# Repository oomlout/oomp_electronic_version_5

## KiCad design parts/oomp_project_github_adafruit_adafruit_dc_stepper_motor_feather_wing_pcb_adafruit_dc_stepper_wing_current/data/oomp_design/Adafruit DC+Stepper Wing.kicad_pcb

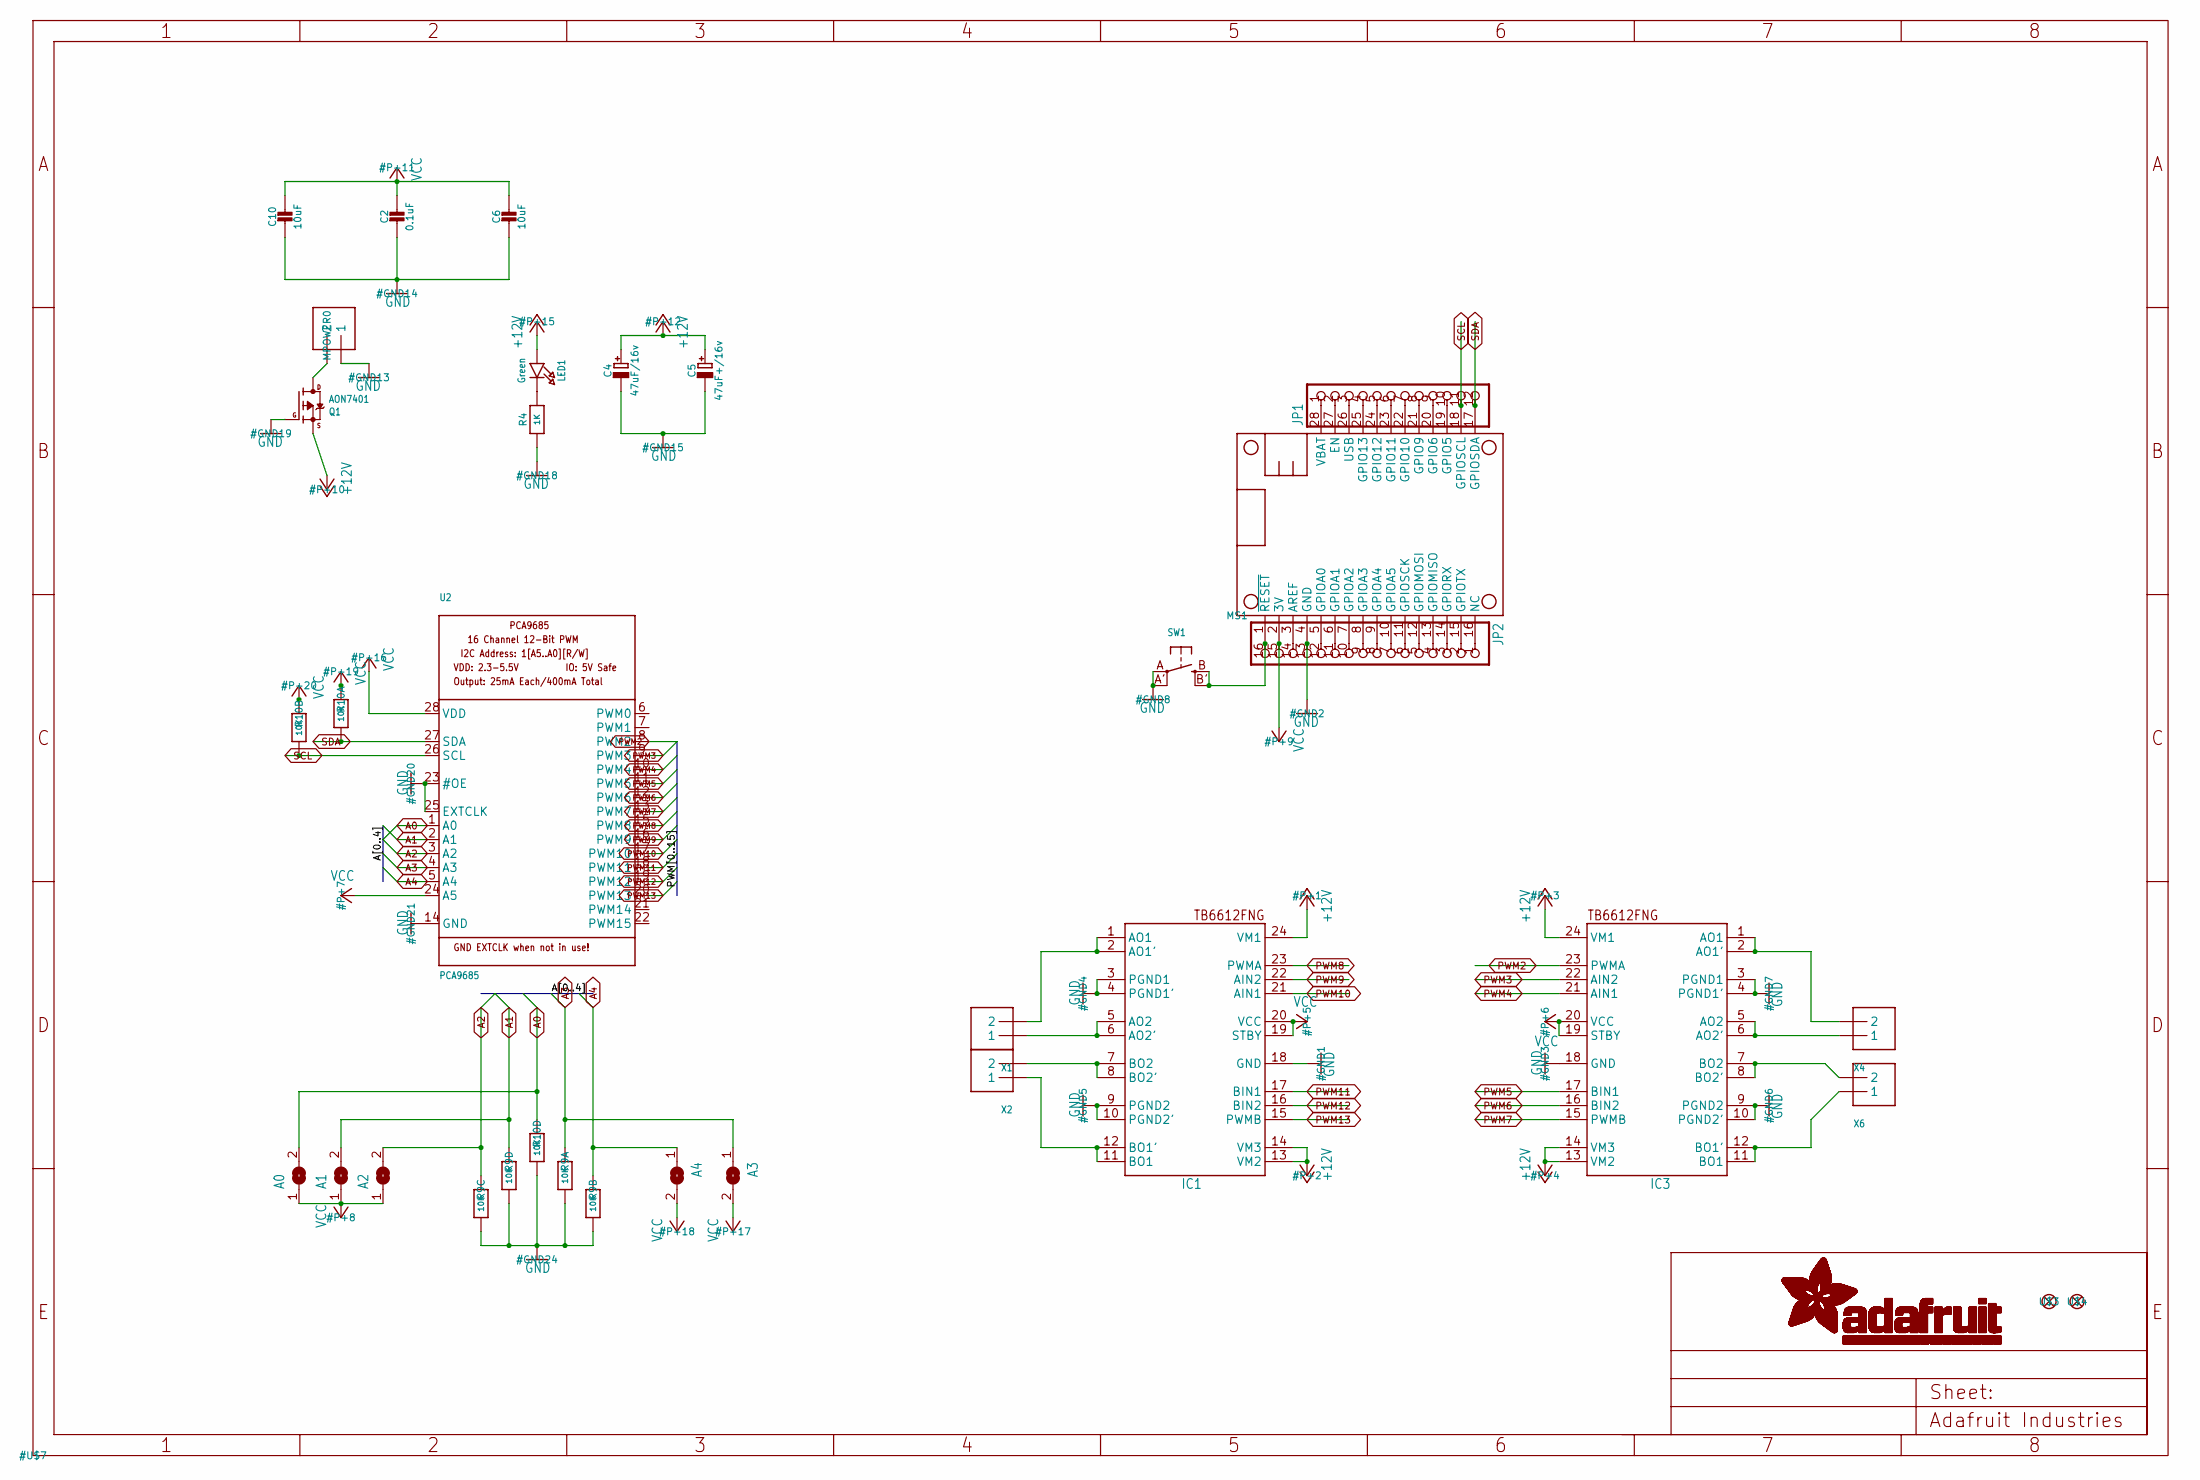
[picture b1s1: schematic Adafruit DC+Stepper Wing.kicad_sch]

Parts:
A0, A1, A2, A3, A4: SOLDERJUMPERREFLOW_NOPASTE; SOLDERJUMPER_REFLOW_NOPASTE
C2: 0.1uF; 0805-NO
C4: 47uF/16v; PANASONIC_C
C5: 47uF+/16v; PANASONIC_C
C6, C10: 10uF; 0805-NO
IC1, IC3: TB6612FNG; SSOP24
JP1: HEADER-1X12; 1X12_ROUND
JP2: HEADER-1X16ROUND; 1X16_ROUND
LED1: Green; CHIPLED_0805_NOOUTLINE
MPOWER0: 1X2-3.5MM
MS1: FEATHERWING
Q1: AON7401; POWERDI3333
R4: 1K; 0805-NO
R9, R10: 10K; RESPACK_4X0603
SW1: SWITCH_TACT_SMT4.6X2.8; BTN_KMR2_4.6X2.8
U2: PCA9685; TSSOP28
U$3, U$4: FIDUCIAL""; FIDUCIAL_1MM
X1, X2, X4, X6: TERMBLOCK_1X2; TERMBLOCK_1X2-3.5MM

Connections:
+12V: C4.+, C5.+, IC1.13 (VM2), IC1.14 (VM3), IC1.24 (VM1), IC3.13 (VM2), IC3.14 (VM3), IC3.24 (VM1), LED1.A, Q1.1 (S), Q1.2 (S), Q1.3 (S)
A0: A0.2, R10.4 (1), U2.1 (A0)
A1: A1.2, R9.5 (2), U2.2 (A1)
A2: A2.2, R9.6 (2), U2.3 (A2)
A3: A3.1, R9.8 (2), U2.4 (A3)
A4: A4.1, R9.7 (2), U2.5 (A4)
GND: C2.2, C4.-, C5.-, C6.2, C10.2, IC1.3 (PGND1), IC1.4 (PGND1'), IC1.9 (PGND2), IC1.10 (PGND2'), IC1.18 (GND), IC3.3 (PGND1), IC3.4 (PGND1'), IC3.9 (PGND2), IC3.10 (PGND2'), IC3.18 (GND), JP2.13, MPOWER0.1, MS1.4 (GND), Q1.4 (G), R4.1, R9.1, R9.2 (1), R9.3 (1), R9.4 (1), R10.5 (2), SW1.A, SW1.A' (P1), U2.14 (GND), U2.23 (#OE), U2.25 (EXTCLK)
unnamed: JP1.2, MS1.27 (EN)
unnamed: JP1.4, MS1.25 (GPIO13)
unnamed: MPOWER0.2, Q1.5678 (D)
unnamed: IC1.1 (AO1), IC1.2 (AO1'), X1.2
unnamed: JP1.5, MS1.24 (GPIO12)
unnamed: IC1.5 (AO2), IC1.6 (AO2'), X1.1
unnamed: IC1.7 (BO2), IC1.8 (BO2'), X2.2
unnamed: JP1.6, MS1.23 (GPIO11)
unnamed: IC1.11 (BO1), IC1.12 (BO1'), X2.1
unnamed: JP1.7, MS1.22 (GPIO10)
unnamed: JP1.8, MS1.21 (GPIO9)
unnamed: IC3.1 (AO1), IC3.2 (AO1'), X4.2
unnamed: JP1.9, MS1.20 (GPIO6)
unnamed: IC3.5 (AO2), IC3.6 (AO2'), X4.1
unnamed: IC3.7 (BO2), IC3.8 (BO2'), X6.2
unnamed: JP1.10, MS1.19 (GPIO5)
unnamed: IC3.11 (BO1), IC3.12 (BO1'), X6.1
unnamed: JP2.1, MS1.16 (NC)
unnamed: JP2.2, MS1.15 (GPIOTX)
unnamed: JP2.3, MS1.14 (GPIORX)
unnamed: JP2.4, MS1.13 (GPIOMISO)
unnamed: JP2.5, MS1.12 (GPIOMOSI)
unnamed: JP2.6, MS1.11 (GPIOSCK)
unnamed: JP2.7, MS1.10 (GPIOA5)
unnamed: JP2.8, MS1.9 (GPIOA4)
unnamed: JP2.9, MS1.8 (GPIOA3)
unnamed: JP2.10, MS1.7 (GPIOA2)
unnamed: JP2.11, MS1.6 (GPIOA1)
unnamed: JP2.12, MS1.5 (GPIOA0)
unnamed: JP2.14, MS1.3 (AREF)
unnamed: JP2.16, MS1.1 (~RESET), SW1.B (S), SW1.B' (S1)
unnamed: LED1.C, R4.2
PWM2: IC3.23 (PWMA), U2.8 (PWM2)
PWM3: IC3.22 (AIN2), U2.9 (PWM3)
PWM4: IC3.21 (AIN1), U2.10 (PWM4)
PWM5: IC3.17 (BIN1), U2.11 (PWM5)
PWM6: IC3.16 (BIN2), U2.12 (PWM6)
PWM7: IC3.15 (PWMB), U2.13 (PWM7)
PWM8: IC1.23 (PWMA), U2.15 (PWM8)
PWM9: IC1.22 (AIN2), U2.16 (PWM9)
PWM10: IC1.21 (AIN1), U2.17 (PWM10)
PWM11: IC1.17 (BIN1), U2.18 (PWM11)
PWM12: IC1.16 (BIN2), U2.19 (PWM12)
PWM13: IC1.15 (PWMB), U2.20 (PWM13)
SCL: JP1.11, MS1.18 (GPIOSCL), R10.2 (1), U2.26 (SCL)
SDA: JP1.12, MS1.17 (GPIOSDA), R10.1, U2.27 (SDA)
USB: JP1.3, MS1.26 (USB)
VBAT: JP1.1, MS1.28 (VBAT)
VCC: A0.1, A1.1, A2.1, A3.2, A4.2, C2.1, C6.1, C10.1, IC1.19 (STBY), IC1.20 (VCC), IC3.19 (STBY), IC3.20 (VCC), JP2.15, MS1.2 (3V), R10.7 (2), R10.8 (2), U2.24 (A5), U2.28 (VDD)

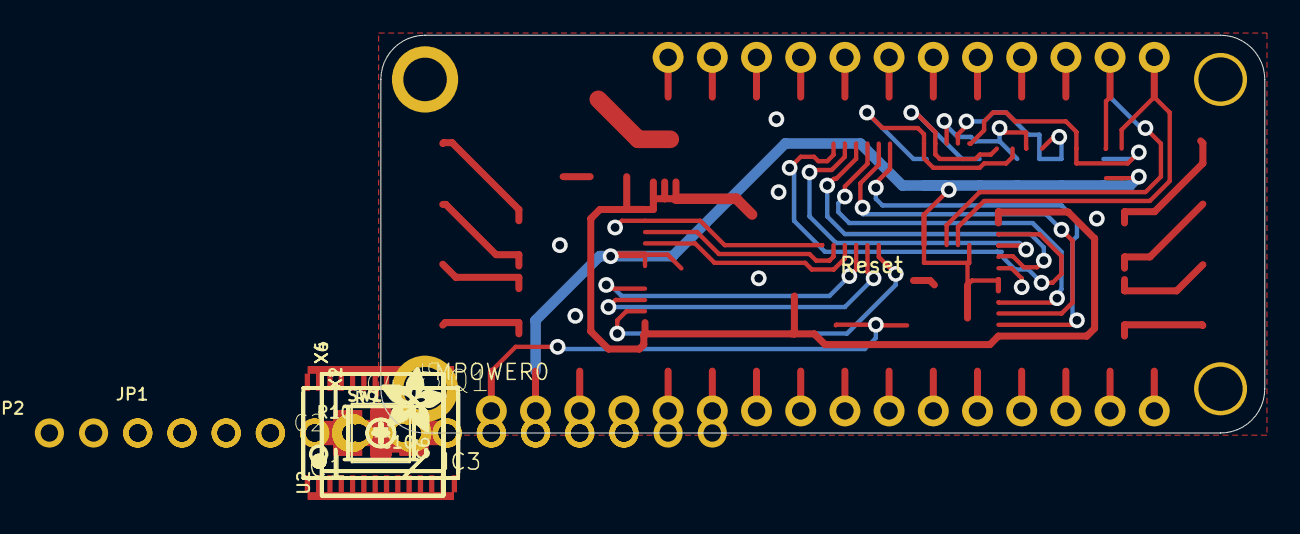
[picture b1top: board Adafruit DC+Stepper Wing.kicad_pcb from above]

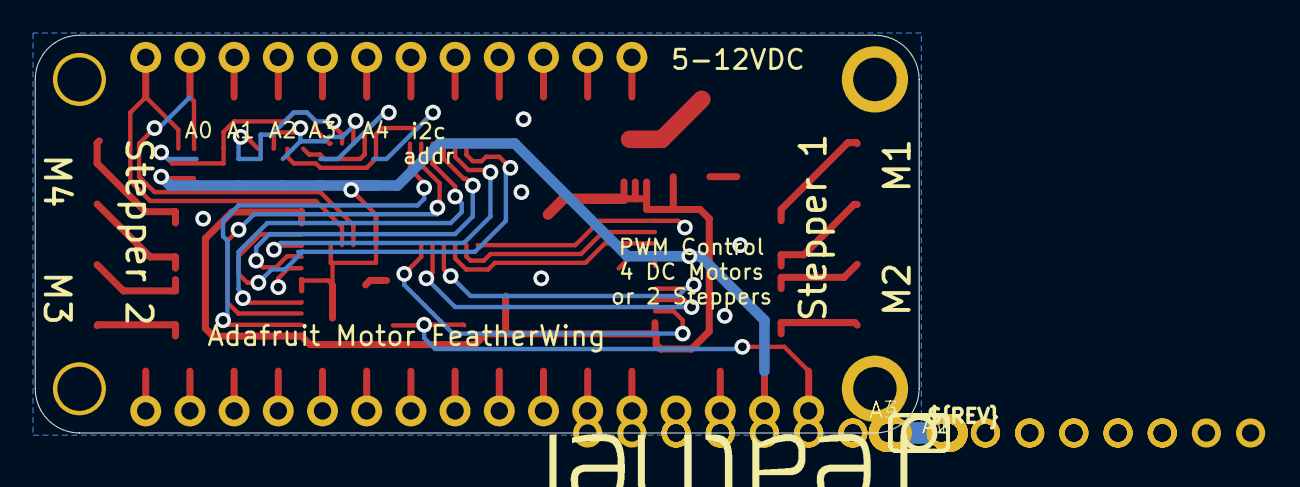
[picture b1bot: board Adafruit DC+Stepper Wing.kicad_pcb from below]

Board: 16 copper layers, 50.8 x 22.9 mm, 34 parts (7 on the bottom side), 56 nets.

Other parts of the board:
U$1: SYMBOL_PLUS
U$2: SYMBOL_MINUS
U$5: ADAFRUIT_3.5MM
U$6: FEATHERLOGO
U$8: PCBFEAT-REV-040

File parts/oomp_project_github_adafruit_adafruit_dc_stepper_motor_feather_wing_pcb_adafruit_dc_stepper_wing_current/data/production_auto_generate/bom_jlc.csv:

Comment,Designator,Footprint,LCSC Part #
,JP1,Adafruit DC+Stepper Wing-import-fps:1X12_ROUND,C7501588
,JP2,Adafruit DC+Stepper Wing-import-fps:1X16_ROUND,C7501270
,U$5,Adafruit DC+Stepper Wing-import-fps:ADAFRUIT_3.5MM,
,SW1,Adafruit DC+Stepper Wing-import-fps:BTN_KMR2_4.6X2.8,
,U$6,Adafruit DC+Stepper Wing-import-fps:FEATHERLOGO,
,U$8,Adafruit DC+Stepper Wing-import-fps:PCBFEAT-REV-040,
,"A0,A1,A2,A3,A4",Adafruit DC+Stepper Wing-import-fps:SOLDERJUMPER_REFLOW_NOPASTE,
,U$2,Adafruit DC+Stepper Wing-import-fps:SYMBOL_MINUS,
,U$1,Adafruit DC+Stepper Wing-import-fps:SYMBOL_PLUS,
,"X1,X2,X4,X6",Adafruit DC+Stepper Wing-import-fps:TERMBLOCK_1X2-3.5MM,
0.1uF,C2,Adafruit DC+Stepper Wing-import-fps:0805-NO,
10K,"R9,R10",Adafruit DC+Stepper Wing-import-fps:RESPACK_4X0603,C98220
10uF,"C6,C10",Adafruit DC+Stepper Wing-import-fps:0805-NO,
1K,R4,Adafruit DC+Stepper Wing-import-fps:0805-NO,C17513
1X2-3.5MM,MPOWER0,Adafruit DC+Stepper Wing-import-fps:1X2-3.5MM,C492401
47uF+/16v,C5,Adafruit DC+Stepper Wing-import-fps:PANASONIC_C,
47uF/16v,C4,Adafruit DC+Stepper Wing-import-fps:PANASONIC_C,
AON7401,Q1,Adafruit DC+Stepper Wing-import-fps:POWERDI3333,
FEATHERWING,MS1,Adafruit DC+Stepper Wing-import-fps:FEATHERWING,
"FIDUCIAL""""","U$3,U$4",Adafruit DC+Stepper Wing-import-fps:FIDUCIAL_1MM,
Green,LED1,Adafruit DC+Stepper Wing-import-fps:CHIPLED_0805_NOOUTLINE,
PCA9685,U2,Adafruit DC+Stepper Wing-import-fps:TSSOP28,
TB6612FNG,"IC1,IC3",Adafruit DC+Stepper Wing-import-fps:SSOP24,

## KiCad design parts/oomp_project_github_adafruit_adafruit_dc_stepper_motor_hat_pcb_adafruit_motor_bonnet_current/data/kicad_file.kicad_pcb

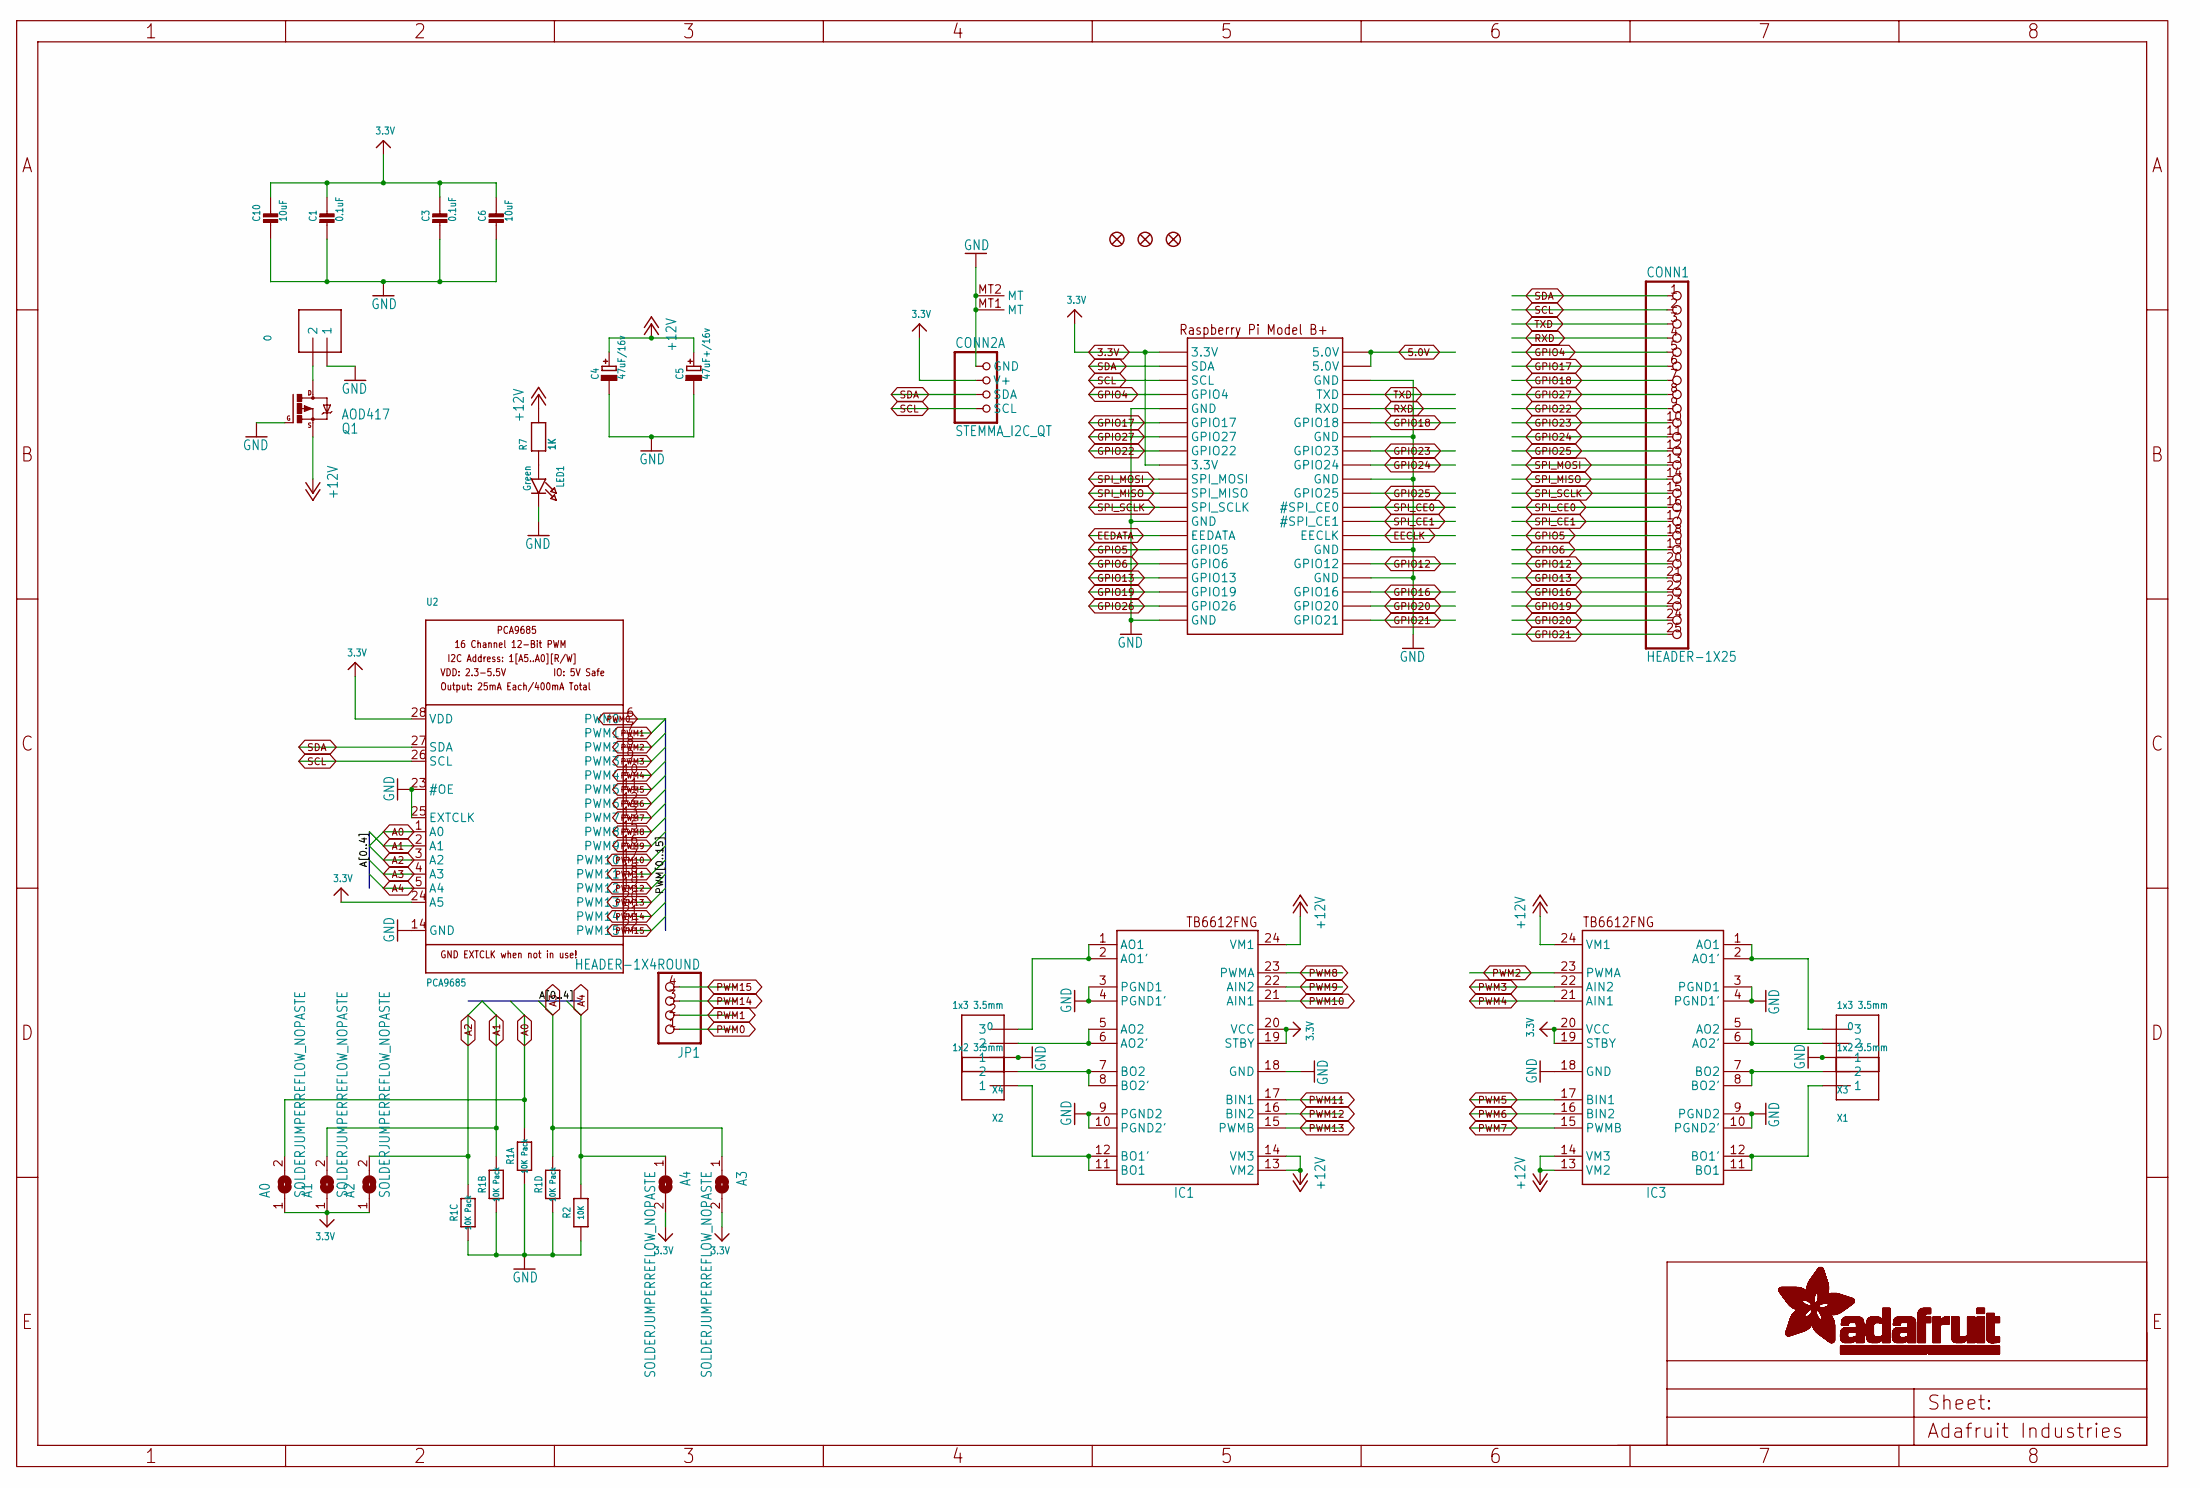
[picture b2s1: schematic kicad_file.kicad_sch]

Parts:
A0, A1, A2, A3, A4: SOLDERJUMPERREFLOW_NOPASTE; SOLDERJUMPER_REFLOW_NOPASTE
C1, C3: 0.1uF; 0603-NO
C4: 47uF/16v; PANASONIC_C
C5: 47uF+/16v; PANASONIC_C
C6, C10: 10uF; 0805-NO
CONN1: HEADER-1X25; 1X25_ROUND_70MIL
CONN2: STEMMA_I2C_QT; JST_SH4; LCSC C2905006
FID1, FID2, FID3: FIDUCIAL_1MM
IC1, IC3: TB6612FNG; SSOP24
JP1: HEADER-1X4ROUND; 1X04_ROUND
LED1: Green; CHIPLED_0805_NOOUTLINE
MPOWER0: 1x2 3.5mm; TERMBLOCK_1X2-3.5MM
Q1: AOD417; D-PAK_TO252AA
R1: 10K Pack; RESPACK_4X0603
R2: 10K; 0603-NO
R7: 1K; 0603-NO
RPI1: RASPBERRYPI_BPLUS_BONNET_THMSMT; PI_BONNET_THMSMT
U2: PCA9685; TSSOP28
X1, X2: 1x2 3.5mm; TERMBLOCK_1X2-3.5MM
X3, X4: 1x3 3.5mm; TERMBLOCK_1X3-3.5MM

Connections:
3.3V: A0.1, A1.1, A2.1, A3.2, A4.2, C1.1, C3.1, C6.1, C10.1, CONN2.2 (V+), IC1.19 (STBY), IC1.20 (VCC), IC3.19 (STBY), IC3.20 (VCC), RPI1.1 (3.3V), RPI1.17 (3.3V), RPI1.S1 (3.3V), RPI1.S17 (3.3V), U2.24 (A5), U2.28 (VDD)
5.0V: RPI1.2 (5.0V), RPI1.4 (5.0V), RPI1.S2 (5.0V), RPI1.S4 (5.0V)
+12V: C4.+, C5.+, IC1.13 (VM2), IC1.14 (VM3), IC1.24 (VM1), IC3.13 (VM2), IC3.14 (VM3), IC3.24 (VM1), Q1.3 (S), R7.2
A0: A0.2, R1.8 (2), U2.1 (A0)
A1: A1.2, R1.7 (2), U2.2 (A1)
A2: A2.2, R1.6 (2), U2.3 (A2)
A3: A3.1, R1.5 (2), U2.4 (A3)
A4: A4.1, R2.2, U2.5 (A4)
EECLK: RPI1.28 (EECLK), RPI1.S28 (EECLK)
EEDATA: RPI1.27 (EEDATA), RPI1.S27 (EEDATA)
GND: C1.2, C3.2, C4.-, C5.-, C6.2, C10.2, CONN2.1 (GND), CONN2.MT1 (MT), CONN2.MT2 (MT), IC1.3 (PGND1), IC1.4 (PGND1'), IC1.9 (PGND2), IC1.10 (PGND2'), IC1.18 (GND), IC3.3 (PGND1), IC3.4 (PGND1'), IC3.9 (PGND2), IC3.10 (PGND2'), IC3.18 (GND), LED1.C, MPOWER0.1, Q1.1 (G), R1.1, R1.2 (1), R1.3 (1), R1.4 (1), R2.1, RPI1.6 (GND), RPI1.9 (GND), RPI1.14 (GND), RPI1.20 (GND), RPI1.25 (GND), RPI1.30 (GND), RPI1.34 (GND), RPI1.39 (GND), RPI1.S6 (GND), RPI1.S9 (GND), RPI1.S14 (GND), RPI1.S20 (GND), RPI1.S25 (GND), RPI1.S30 (GND), RPI1.S34 (GND), RPI1.S39 (GND), U2.14 (GND), U2.23 (#OE), U2.25 (EXTCLK), X3.1, X4.1
GPIO4: CONN1.5, RPI1.7 (GPIO4), RPI1.S7 (GPIO4)
GPIO5: CONN1.18, RPI1.29 (GPIO5), RPI1.S29 (GPIO5)
GPIO6: CONN1.19, RPI1.31 (GPIO6), RPI1.S31 (GPIO6)
GPIO12: CONN1.20, RPI1.32 (GPIO12), RPI1.S32 (GPIO12)
GPIO13: CONN1.21, RPI1.33 (GPIO13), RPI1.S33 (GPIO13)
GPIO16: CONN1.22, RPI1.36 (GPIO16), RPI1.S36 (GPIO16)
GPIO17: CONN1.6, RPI1.11 (GPIO17), RPI1.S11 (GPIO17)
GPIO18: CONN1.7, RPI1.12 (GPIO18), RPI1.S12 (GPIO18)
GPIO19: CONN1.23, RPI1.35 (GPIO19), RPI1.S35 (GPIO19)
GPIO20: CONN1.24, RPI1.38 (GPIO20), RPI1.S38 (GPIO20)
GPIO21: CONN1.25, RPI1.40 (GPIO21), RPI1.S40 (GPIO21)
GPIO22: CONN1.9, RPI1.15 (GPIO22), RPI1.S15 (GPIO22)
GPIO23: CONN1.10, RPI1.16 (GPIO23), RPI1.S16 (GPIO23)
GPIO24: CONN1.11, RPI1.18 (GPIO24), RPI1.S18 (GPIO24)
GPIO25: CONN1.12, RPI1.22 (GPIO25), RPI1.S22 (GPIO25)
GPIO26: RPI1.37 (GPIO26), RPI1.S37 (GPIO26)
GPIO27: CONN1.8, RPI1.13 (GPIO27), RPI1.S13 (GPIO27)
M1A: IC1.1 (AO1), IC1.2 (AO1'), X4.3
M1B: IC1.5 (AO2), IC1.6 (AO2'), X4.2
M2A: IC1.11 (BO1), IC1.12 (BO1'), X2.1
M2B: IC1.7 (BO2), IC1.8 (BO2'), X2.2
M3A: IC3.1 (AO1), IC3.2 (AO1'), X3.3
M3B: IC3.5 (AO2), IC3.6 (AO2'), X3.2
M4A: IC3.11 (BO1), IC3.12 (BO1'), X1.1
M4B: IC3.7 (BO2), IC3.8 (BO2'), X1.2
unnamed: LED1.A, R7.1
PWM0: JP1.1, U2.6 (PWM0)
PWM1: JP1.2, U2.7 (PWM1)
PWM2: IC3.23 (PWMA), U2.8 (PWM2)
PWM3: IC3.22 (AIN2), U2.9 (PWM3)
PWM4: IC3.21 (AIN1), U2.10 (PWM4)
PWM5: IC3.17 (BIN1), U2.11 (PWM5)
PWM6: IC3.16 (BIN2), U2.12 (PWM6)
PWM7: IC3.15 (PWMB), U2.13 (PWM7)
PWM8: IC1.23 (PWMA), U2.15 (PWM8)
PWM9: IC1.22 (AIN2), U2.16 (PWM9)
PWM10: IC1.21 (AIN1), U2.17 (PWM10)
PWM11: IC1.17 (BIN1), U2.18 (PWM11)
PWM12: IC1.16 (BIN2), U2.19 (PWM12)
PWM13: IC1.15 (PWMB), U2.20 (PWM13)
PWM14: JP1.3, U2.21 (PWM14)
PWM15: JP1.4, U2.22 (PWM15)
RXD: CONN1.4, RPI1.10 (RXD), RPI1.S10 (RXD)
SCL: CONN1.2, CONN2.4 (SCL), RPI1.5 (SCL), RPI1.S5 (SCL), U2.26 (SCL)
SDA: CONN1.1, CONN2.3 (SDA), RPI1.3 (SDA), RPI1.S3 (SDA), U2.27 (SDA)
SPI_CE0: CONN1.16, RPI1.24 (#SPI_CE0), RPI1.S24 (#SPI_CE0)
SPI_CE1: CONN1.17, RPI1.26 (#SPI_CE1), RPI1.S26 (#SPI_CE1)
SPI_MISO: CONN1.14, RPI1.21 (SPI_MISO), RPI1.S21 (SPI_MISO)
SPI_MOSI: CONN1.13, RPI1.19 (SPI_MOSI), RPI1.S19 (SPI_MOSI)
SPI_SCLK: CONN1.15, RPI1.23 (SPI_SCLK), RPI1.S23 (SPI_SCLK)
TXD: CONN1.3, RPI1.8 (TXD), RPI1.S8 (TXD)
VMOTOR: MPOWER0.2, Q1.4 (D)

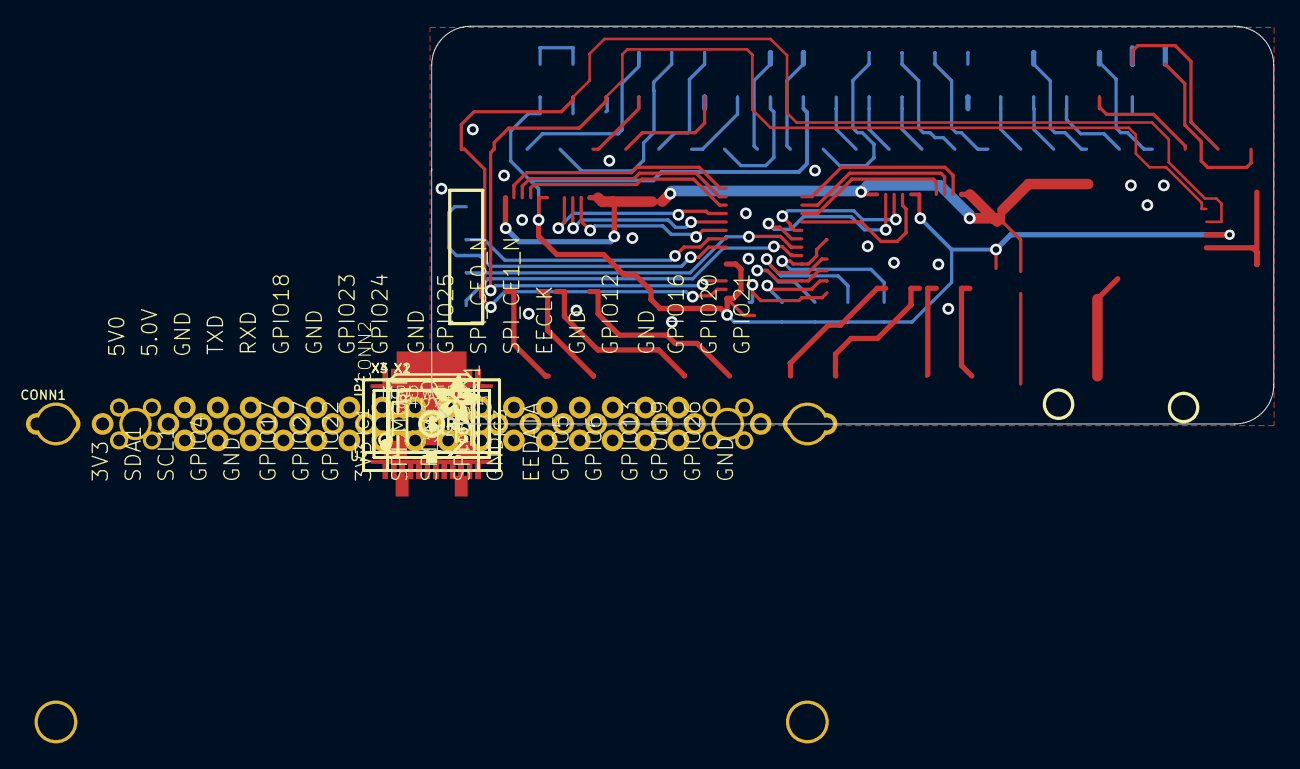
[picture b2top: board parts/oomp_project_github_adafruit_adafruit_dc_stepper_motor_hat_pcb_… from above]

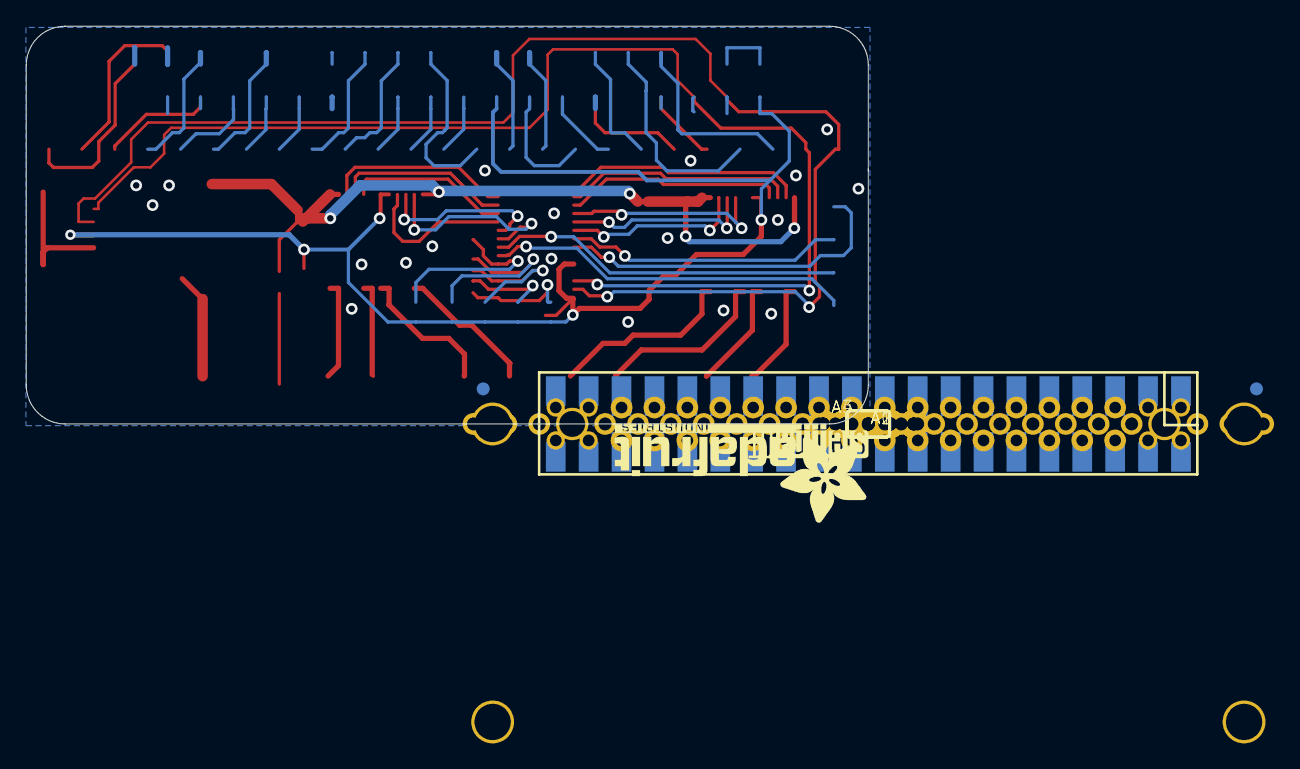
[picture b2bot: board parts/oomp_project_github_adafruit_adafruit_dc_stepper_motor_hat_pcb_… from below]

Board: 2 copper layers, 65.0 x 30.7 mm, 82 parts (13 on the bottom side), 63 nets.

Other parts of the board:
PLABEL0: PLABEL0
PLABEL1: PLABEL1
PLABEL2: PLABEL2
PLABEL3: PLABEL3
PLABEL4: PLABEL4
PLABEL5: PLABEL5
PLABEL6: PLABEL6
PLABEL7: PLABEL7
PLABEL8: PLABEL8
PLABEL9: PLABEL9
PLABEL10: PLABEL10
PLABEL11: PLABEL11
PLABEL12: PLABEL12
PLABEL13: PLABEL13
PLABEL14: PLABEL14
PLABEL15: PLABEL15
PLABEL16: PLABEL16
PLABEL17: PLABEL17
PLABEL18: PLABEL18
PLABEL19: PLABEL19
PLABEL20: PLABEL20
PLABEL21: PLABEL21
PLABEL22: PLABEL22
PLABEL23: PLABEL23
PLABEL24: PLABEL24
PLABEL25: PLABEL25
PLABEL26: PLABEL26
PLABEL27: PLABEL27
PLABEL28: PLABEL28
PLABEL29: PLABEL29
PLABEL30: PLABEL30
PLABEL31: PLABEL31
PLABEL33: PLABEL33
PLABEL34: PLABEL34
PLABEL35: PLABEL35
PLABEL36: PLABEL36
PLABEL37: PLABEL37
PLABEL38: PLABEL38
PLABEL39: PLABEL39
PLABEL40: PLABEL40
PLABEL41: PLABEL41
PLABEL42: PLABEL42
PLABEL43: PLABEL43
PLABEL44: PLABEL44
PLABEL45: PLABEL45
PLABEL46: PLABEL46
PLABEL47: PLABEL47
U$6: PCBFEAT-REV-040
U$8: ADAFRUIT_TEXT_20MM
U$14: ADAFRUIT_3.5MM
U$15: STEMMAQT

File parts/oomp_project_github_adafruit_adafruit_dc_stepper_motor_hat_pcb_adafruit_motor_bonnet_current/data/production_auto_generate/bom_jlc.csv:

Comment,Designator,Footprint,LCSC Part #
,JP1,Adafruit Motor Bonnet Rev B-import-fps:1X04_ROUND,C42431795
,U$14,Adafruit Motor Bonnet Rev B-import-fps:ADAFRUIT_3.5MM,
,U$8,Adafruit Motor Bonnet Rev B-import-fps:ADAFRUIT_TEXT_20MM,
,U$6,Adafruit Motor Bonnet Rev B-import-fps:PCBFEAT-REV-040,
,PLABEL0,Adafruit Motor Bonnet Rev B-import-fps:PLABEL0,
,PLABEL1,Adafruit Motor Bonnet Rev B-import-fps:PLABEL1,
,PLABEL10,Adafruit Motor Bonnet Rev B-import-fps:PLABEL10,
,PLABEL11,Adafruit Motor Bonnet Rev B-import-fps:PLABEL11,
,PLABEL12,Adafruit Motor Bonnet Rev B-import-fps:PLABEL12,
,PLABEL13,Adafruit Motor Bonnet Rev B-import-fps:PLABEL13,
,PLABEL14,Adafruit Motor Bonnet Rev B-import-fps:PLABEL14,
,PLABEL15,Adafruit Motor Bonnet Rev B-import-fps:PLABEL15,
,PLABEL16,Adafruit Motor Bonnet Rev B-import-fps:PLABEL16,
,PLABEL17,Adafruit Motor Bonnet Rev B-import-fps:PLABEL17,
,PLABEL18,Adafruit Motor Bonnet Rev B-import-fps:PLABEL18,
,PLABEL19,Adafruit Motor Bonnet Rev B-import-fps:PLABEL19,
,PLABEL2,Adafruit Motor Bonnet Rev B-import-fps:PLABEL2,
,PLABEL20,Adafruit Motor Bonnet Rev B-import-fps:PLABEL20,
,PLABEL21,Adafruit Motor Bonnet Rev B-import-fps:PLABEL21,
,PLABEL22,Adafruit Motor Bonnet Rev B-import-fps:PLABEL22,
,PLABEL23,Adafruit Motor Bonnet Rev B-import-fps:PLABEL23,
,PLABEL24,Adafruit Motor Bonnet Rev B-import-fps:PLABEL24,
,PLABEL25,Adafruit Motor Bonnet Rev B-import-fps:PLABEL25,
,PLABEL26,Adafruit Motor Bonnet Rev B-import-fps:PLABEL26,
,PLABEL27,Adafruit Motor Bonnet Rev B-import-fps:PLABEL27,
,PLABEL28,Adafruit Motor Bonnet Rev B-import-fps:PLABEL28,
,PLABEL29,Adafruit Motor Bonnet Rev B-import-fps:PLABEL29,
,PLABEL3,Adafruit Motor Bonnet Rev B-import-fps:PLABEL3,
,PLABEL30,Adafruit Motor Bonnet Rev B-import-fps:PLABEL30,
,PLABEL31,Adafruit Motor Bonnet Rev B-import-fps:PLABEL31,
,PLABEL33,Adafruit Motor Bonnet Rev B-import-fps:PLABEL33,
,PLABEL34,Adafruit Motor Bonnet Rev B-import-fps:PLABEL34,
,PLABEL35,Adafruit Motor Bonnet Rev B-import-fps:PLABEL35,
,PLABEL36,Adafruit Motor Bonnet Rev B-import-fps:PLABEL36,
,PLABEL37,Adafruit Motor Bonnet Rev B-import-fps:PLABEL37,
,PLABEL38,Adafruit Motor Bonnet Rev B-import-fps:PLABEL38,
,PLABEL39,Adafruit Motor Bonnet Rev B-import-fps:PLABEL39,
,PLABEL4,Adafruit Motor Bonnet Rev B-import-fps:PLABEL4,
,PLABEL40,Adafruit Motor Bonnet Rev B-import-fps:PLABEL40,
,PLABEL41,Adafruit Motor Bonnet Rev B-import-fps:PLABEL41,
,PLABEL42,Adafruit Motor Bonnet Rev B-import-fps:PLABEL42,
,PLABEL43,Adafruit Motor Bonnet Rev B-import-fps:PLABEL43,
,PLABEL44,Adafruit Motor Bonnet Rev B-import-fps:PLABEL44,
,PLABEL45,Adafruit Motor Bonnet Rev B-import-fps:PLABEL45,
,PLABEL46,Adafruit Motor Bonnet Rev B-import-fps:PLABEL46,
,PLABEL47,Adafruit Motor Bonnet Rev B-import-fps:PLABEL47,
,PLABEL5,Adafruit Motor Bonnet Rev B-import-fps:PLABEL5,
,PLABEL6,Adafruit Motor Bonnet Rev B-import-fps:PLABEL6,
,PLABEL7,Adafruit Motor Bonnet Rev B-import-fps:PLABEL7,
,PLABEL8,Adafruit Motor Bonnet Rev B-import-fps:PLABEL8,
,PLABEL9,Adafruit Motor Bonnet Rev B-import-fps:PLABEL9,
,"A0,A1,A2,A3,A4",Adafruit Motor Bonnet Rev B-import-fps:SOLDERJUMPER_REFLOW_NOPASTE,
,U$15,Adafruit Motor Bonnet Rev B-import-fps:STEMMAQT,
0.1uF,"C1,C3",Adafruit Motor Bonnet Rev B-import-fps:0603-NO,C14663
10K,R2,Adafruit Motor Bonnet Rev B-import-fps:0603-NO,C98220
10K Pack,R1,Adafruit Motor Bonnet Rev B-import-fps:RESPACK_4X0603,C98220
10uF,"C6,C10",Adafruit Motor Bonnet Rev B-import-fps:0805-NO,
1K,R7,Adafruit Motor Bonnet Rev B-import-fps:0603-NO,C2907002
1x2 3.5mm,"MPOWER0,X1,X2",Adafruit Motor Bonnet Rev B-import-fps:TERMBLOCK_1X2-3.5MM,
1x3 3.5mm,"X3,X4",Adafruit Motor Bonnet Rev B-import-fps:TERMBLOCK_1X3-3.5MM,
47uF+/16v,C5,Adafruit Motor Bonnet Rev B-import-fps:PANASONIC_C,
47uF/16v,C4,Adafruit Motor Bonnet Rev B-import-fps:PANASONIC_C,
AOD417,Q1,Adafruit Motor Bonnet Rev B-import-fps:D-PAK_TO252AA,
Green,LED1,Adafruit Motor Bonnet Rev B-import-fps:CHIPLED_0805_NOOUTLINE,
HEADER-1X25,CONN1,Adafruit Motor Bonnet Rev B-import-fps:1X25_ROUND_70MIL,C2883713
PCA9685,U2,Adafruit Motor Bonnet Rev B-import-fps:TSSOP28,
RASPBERRYPI_BPLUS_BONNET_THMSMT,RPI1,Adafruit Motor Bonnet Rev B-import-fps:PI_BONNET_THMSMT,
STEMMA_I2C_QT,CONN2,Adafruit Motor Bonnet Rev B-import-fps:JST_SH4,C160404
TB6612FNG,"IC1,IC3",Adafruit Motor Bonnet Rev B-import-fps:SSOP24,
